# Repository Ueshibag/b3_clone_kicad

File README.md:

# B3 clone KiCad projects, symbols and footprints libraries

## drawbars

A set of 4 interconnected PCBs controlling 38 potentiometers. The left most PCB houses
an Arduino Nano Every which analog to digital converters are used to collect drawbars
positions and send the corresponding MIDI messages to the B3 emulator software (setBfree) running on a Raspberry Pi.

## keyboards

Scans both Fatar keyboards and sends MIDI messages to setBfree

## percussions_expr_pedal

Scans the percussion control switches and performs analog to digital conversion for the
expression pedal. Signals are routed towards the vibrato_chorus_leslie PCB.

## rpi_extension

This is merely a connection PCB for other boards to connect to the Raspberry PI.

## vibrato_chorus_leslie

Scans the vibrato and chorus switches as well as the Leslie 3-position switch (stop/slow/fast).
Gathers signals from the percussions_expr_pedal PCB. Houses an Arduino Nano Every which sends
MIDI messages to setBfree.

## vibrato_chorus_rotary_switch

A small PCB on which the 6-position rotary switch is soldered. This PCB is connected to the
vibrato_chorus_leslie board.

## volume_reverb_overdrive

This board houses three rotary encoders to control IQaudio PiDAC+ volume, setBfree reverb and overdrive. The overdrive rotary switch embeds a push button to safely power down the Raspberry PI.

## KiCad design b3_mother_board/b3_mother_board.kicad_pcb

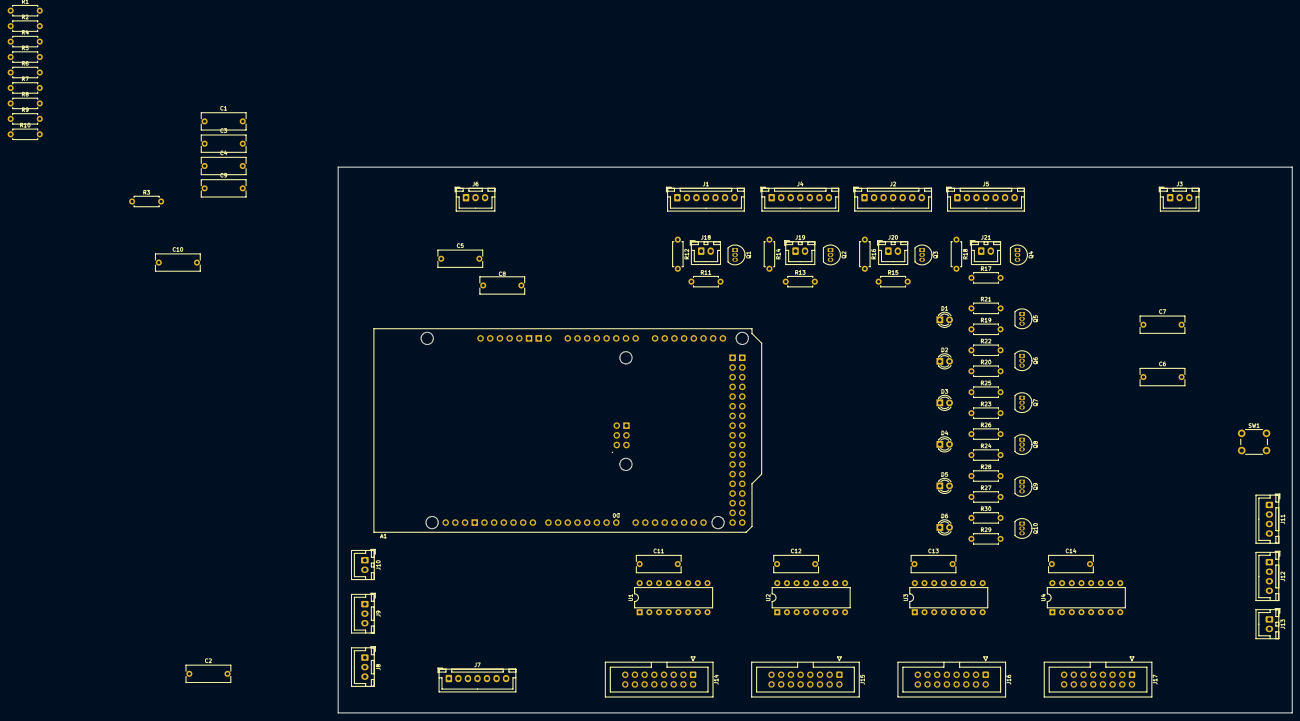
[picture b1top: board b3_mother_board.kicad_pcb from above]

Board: 2 copper layers, 250.0 x 143.0 mm, 87 parts (1 on the bottom side), 127 nets, no tracks yet.

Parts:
A1: Arduino_Mega2560_R3_Shield
C1, C2, C3, C4, C5, C6, C7, C8, C9, C10, C11, C12, C13, C14: 100n; C_Rect_L11.5mm_W4.3mm_P10.00mm_MKT
D1: Keyboards; LED_D3.0mm
D2: Vib/Chr; LED_D3.0mm
D3: Drawbars; LED_D3.0mm
D4: Percussions; LED_D3.0mm
D5: Leslie; LED_D3.0mm
D6: Expression Ped.; LED_D3.0mm
J1: Drawbars_1; JST_XH_B7B-XH-A_1x07_P2.50mm_Vertical
J2: Drawbars_3; JST_XH_B7B-XH-A_1x07_P2.50mm_Vertical
J3: Expression Pedal; JST_XH_B3B-XH-A_1x03_P2.50mm_Vertical
J4: Drawbars_2; JST_XH_B7B-XH-A_1x07_P2.50mm_Vertical
J5: Drawbars_4; JST_XH_B7B-XH-A_1x07_P2.50mm_Vertical
J6: Leslie; JST_XH_B3B-XH-A_1x03_P2.50mm_Vertical
J7: V/C Rotary Knob; JST_XH_B7B-XH-A_1x07_P2.50mm_Vertical
J8: Ovrdrv/Vib LEDs; JST_XH_B3B-XH-A_1x03_P2.50mm_Vertical
J9: Ovrdrv/Vib Switches; JST_XH_B3B-XH-A_1x03_P2.50mm_Vertical
J10: Ovrdrv/Vib PWR; JST_XH_B2B-XH-A_1x02_P2.50mm_Vertical
J11: Percussion LEDs; JST_XH_B4B-XH-A_1x04_P2.50mm_Vertical
J12: Percussion Switches; JST_XH_B4B-XH-A_1x04_P2.50mm_Vertical
J13: Percussion PWR; JST_XH_B2B-XH-A_1x02_P2.50mm_Vertical
J14: Upper Keyboard Left; IDC-Header_2x08_P2.54mm_Vertical
J15: Upper Keyboard Right; IDC-Header_2x08_P2.54mm_Vertical
J16: Lower Keyboard Left; IDC-Header_2x08_P2.54mm_Vertical
J17: Lower Keyboard Right; IDC-Header_2x08_P2.54mm_Vertical
J18: Upper A LED; JST_XH_B2B-XH-A_1x02_P2.50mm_Vertical
J19: Upper B LED; JST_XH_B2B-XH-A_1x02_P2.50mm_Vertical
J20: Lower A LED; JST_XH_B2B-XH-A_1x02_P2.50mm_Vertical
J21: Lower B LED; JST_XH_B2B-XH-A_1x02_P2.50mm_Vertical
Q1, Q2, Q3, Q4, Q5, Q6, Q7, Q8, Q9, Q10: BC547; TO-92_Inline
R1, R2: 68K; R_Axial_DIN0207_L6.3mm_D2.5mm_P7.62mm_Horizontal
R3, R4, R5, R6: 2.2K; R_Axial_DIN0207_L6.3mm_D2.5mm_P7.62mm_Horizontal
R7, R8, R9, R10: 100; R_Axial_DIN0207_L6.3mm_D2.5mm_P7.62mm_Horizontal
R11, R13, R15, R17, R19, R20, R23, R24, R27, R29: 2.8K; R_Axial_DIN0207_L6.3mm_D2.5mm_P7.62mm_Horizontal
R12, R14, R16, R18, R21, R22, R25, R26, R28, R30: 220; R_Axial_DIN0207_L6.3mm_D2.5mm_P7.62mm_Horizontal
SW1: Reset; SW_PUSH_6mm_H4.3mm
U1, U2, U3, U4: 4051; DIP-16_W7.62mm

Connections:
+5V: A1.5V1 (5V), A1.5V2 (SPI_5V), A1.5V3 (5V), A1.5V4 (5V), A1.AREF, C11.1, C12.1, C13.1, C14.1, J1.1, J2.1, J3.1, J4.1, J5.1, J6.1, J10.1, J13.1, R1.1, R12.1, R14.1, R16.1, R18.1, R21.1, R22.1, R25.1, R26.1, R28.1, R30.1, U1.16 (VDD), U2.16 (VDD), U3.16 (VDD), U4.16 (VDD)
/C1: A1.D42, J7.2
/C2: A1.D44, J7.4
/C3: A1.D46, J7.6
/DB_A1_ANLG: A1.A0, C1.1, J1.2
/DB_A2_ANLG: A1.A2, C5.1, J4.2
/DB_A3_ANLG: A1.A4, C2.1, J2.2
/DB_A4_ANLG: A1.A6, C6.1, J5.2
/DB_B1_ANLG: A1.A1, C3.1, J1.3
/DB_B2_ANLG: A1.A3, C7.1, J4.3
/DB_B3_ANLG: A1.A5, C4.1, J2.3
/DB_B4_ANLG: A1.A7, C8.1, J5.3
/DB_MUX_A: A1.D47, J1.4, J2.4, J4.4, J5.4
/DB_MUX_B: A1.D48, J1.5, J2.5, J4.5, J5.5
/DB_MUX_C: A1.D49, J1.6, J2.6, J4.6, J5.6
/DWB_LED: A1.D1 (D1/TX0), R23.1
/EXPR_PEDAL_ANLG: A1.A8, C9.1, J3.2
/EXP_LED: A1.D16 (D16/TX2), R29.1
/KBD_LED: A1.D0 (D0/RX0), R19.1
/LESLIE_ANLG: A1.A9, C10.1, J6.2, R1.2, R2.1
/LO_A_LED: A1.D52 (D52_SCK), R15.1
/LO_B_LED: A1.D53 (D53_CS), R17.1
/LSL_LED: A1.D17 (D17/RX2), R27.1
/OVERDRIVE_LED: A1.D30, J8.1
/OVERDRIVE_SWITCH: A1.D27, J9.1
/PERC_DELAY_LED: A1.D39, J11.3
/PERC_DELAY_SWITCH: A1.D35, J12.3
/PERC_HARMONIC_LED: A1.D40, J11.4
/PERC_HARMONIC_SWITCH: A1.D36, J12.4
/PERC_ON_OFF_LED: A1.D37, J11.1
/PERC_ON_OFF_SWITCH: A1.D33, J12.1
/PERC_VOLUME_LED: A1.D38, J11.2
/PERC_VOLUME_SWITCH: A1.D34, J12.2
/PRC_LED: A1.D18 (D18/TX1), R24.1
/T0: A1.D11, J14.2, J15.2, J16.2, J17.2
/T1: A1.D12, J14.4, J15.4, J16.4, J17.4
/T2: A1.D13, J14.6, J15.6, J16.6, J17.6
/T3: A1.D22, J14.8, J15.8, J16.8, J17.8
/T4: A1.D23, J14.10, J15.10, J16.10, J17.10
/T5: A1.D24, J14.12, J15.12, J16.12, J17.12
/T6: A1.D25, J14.14, J15.14, J16.14, J17.14
/T7: A1.D26, J14.16, J15.16, J16.16, J17.16
/UP_A_LED: A1.D50 (D50_MISO), R11.1
/UP_B_LED: A1.D51 (D51_MOSI), R13.1
/V1: A1.D41, J7.1
/V2: A1.D43, J7.3
/V3: A1.D45, J7.5
/VIBRATO_LOWER_LED: A1.D32, J8.3
/VIBRATO_LOWER_SWITCH: A1.D29, J9.3
/VIBRATO_UPPER_LED: A1.D31, J8.2
/VIBRATO_UPPER_SWITCH: A1.D28, J9.2
/VIB_LED: A1.D19 (D19/RX1), R20.1
/keyboards_control_sub/BRA: A1.D7, R7.1
/keyboards_control_sub/BRA0: J14.3, U1.13 (X0)
/keyboards_control_sub/BRA1: J14.7, U1.14 (X1)
/keyboards_control_sub/BRA2: J14.11, U1.15 (X2)
/keyboards_control_sub/BRA3: J14.15, U1.12 (X3)
/keyboards_control_sub/BRA4: J15.3, U1.1 (X4)
/keyboards_control_sub/BRA5: J15.7, U1.5 (X5)
/keyboards_control_sub/BRA6: J15.11, U1.2 (X6)
/keyboards_control_sub/BRA7: J15.15, U1.4 (X7)
/keyboards_control_sub/BRB: A1.D8, R8.1
/keyboards_control_sub/BRB0: J16.3, U3.13 (X0)
/keyboards_control_sub/BRB1: J16.7, U3.14 (X1)
/keyboards_control_sub/BRB2: J16.11, U3.15 (X2)
/keyboards_control_sub/BRB3: J16.15, U3.12 (X3)
/keyboards_control_sub/BRB4: J17.3, U3.1 (X4)
/keyboards_control_sub/BRB5: J17.7, U3.5 (X5)
/keyboards_control_sub/BRB6: J17.11, U3.2 (X6)
/keyboards_control_sub/BRB7: J17.15, U3.4 (X7)
/keyboards_control_sub/KB_MUX_A: A1.D4, U1.11 (A), U2.11 (A), U3.11 (A), U4.11 (A)
/keyboards_control_sub/KB_MUX_B: A1.D5, U1.10 (B), U2.10 (B), U3.10 (B), U4.10 (B)
/keyboards_control_sub/KB_MUX_C: A1.D6, U1.9 (C), U2.9 (C), U3.9 (C), U4.9 (C)
/keyboards_control_sub/MKA: A1.D9, R9.1
/keyboards_control_sub/MKA0: J14.1, U2.13 (X0)
/keyboards_control_sub/MKA1: J14.5, U2.14 (X1)
/keyboards_control_sub/MKA2: J14.9, U2.15 (X2)
/keyboards_control_sub/MKA3: J14.13, U2.12 (X3)
/keyboards_control_sub/MKA4: J15.1, U2.1 (X4)
/keyboards_control_sub/MKA5: J15.5, U2.5 (X5)
/keyboards_control_sub/MKA6: J15.9, U2.2 (X6)
/keyboards_control_sub/MKA7: J15.13, U2.4 (X7)
/keyboards_control_sub/MKB: A1.D10, R10.1
/keyboards_control_sub/MKB0: J16.1, U4.13 (X0)
/keyboards_control_sub/MKB1: J16.5, U4.14 (X1)
/keyboards_control_sub/MKB2: J16.9, U4.15 (X2)
/keyboards_control_sub/MKB3: J16.13, U4.12 (X3)
/keyboards_control_sub/MKB4: J17.1, U4.1 (X4)
/keyboards_control_sub/MKB5: J17.5, U4.5 (X5)
/keyboards_control_sub/MKB6: J17.9, U4.2 (X6)
/keyboards_control_sub/MKB7: J17.13, U4.4 (X7)
GND: A1.GND1 (GND), A1.GND2 (GND), A1.GND3 (GND), A1.GND4 (SPI_GND), A1.GND5 (GND), A1.GND6 (GND), C1.2, C2.2, C3.2, C4.2, C5.2, C6.2, C7.2, C8.2, C9.2, C10.2, C11.2, C12.2, C13.2, C14.2, J1.7, J2.7, J3.3, J4.7, J5.7, J6.3, J7.7, J10.2, J13.2, Q1.3 (E), Q2.3 (E), Q3.3 (E), Q4.3 (E), Q5.3 (E), Q6.3 (E), Q7.3 (E), Q8.3 (E), Q9.3 (E), Q10.3 (E), R2.2, R3.2, R4.2, R5.2, R6.2, SW1.1, U1.6 (Inh), U1.7 (VEE), U1.8 (VSS), U2.6 (Inh), U2.7 (VEE), U2.8 (VSS), U3.6 (Inh), U3.7 (VEE), U3.8 (VSS), U4.6 (Inh), U4.7 (VEE), U4.8 (VSS)
unnamed: A1.RST1 (RESET), SW1.2
unnamed: D1.2 (A), R21.2
unnamed: D1.1 (K), Q5.1 (C)
unnamed: D2.2 (A), R22.2
unnamed: D2.1 (K), Q6.1 (C)
unnamed: D3.2 (A), R25.2
unnamed: D3.1 (K), Q7.1 (C)
unnamed: D4.2 (A), R26.2
unnamed: D4.1 (K), Q8.1 (C)
unnamed: D5.2 (A), R28.2
unnamed: D5.1 (K), Q9.1 (C)
unnamed: D6.2 (A), R30.2
unnamed: D6.1 (K), Q10.1 (C)
unnamed: J18.1, R12.2
unnamed: J18.2, Q1.1 (C)
unnamed: J19.1, R14.2
unnamed: J19.2, Q2.1 (C)
unnamed: J20.1, R16.2
unnamed: J20.2, Q3.1 (C)
unnamed: J21.1, R18.2
unnamed: J21.2, Q4.1 (C)
unnamed: Q1.2 (B), R11.2
unnamed: Q2.2 (B), R13.2
unnamed: Q3.2 (B), R15.2
unnamed: Q4.2 (B), R17.2
unnamed: Q5.2 (B), R19.2
unnamed: Q6.2 (B), R20.2
unnamed: Q7.2 (B), R23.2
unnamed: Q8.2 (B), R24.2
unnamed: Q9.2 (B), R27.2
unnamed: Q10.2 (B), R29.2
unnamed: R3.1, R7.2, U1.3 (X)
unnamed: R4.1, R9.2, U2.3 (X)
unnamed: R5.1, R8.2, U3.3 (X)
unnamed: R6.1, R10.2, U4.3 (X)

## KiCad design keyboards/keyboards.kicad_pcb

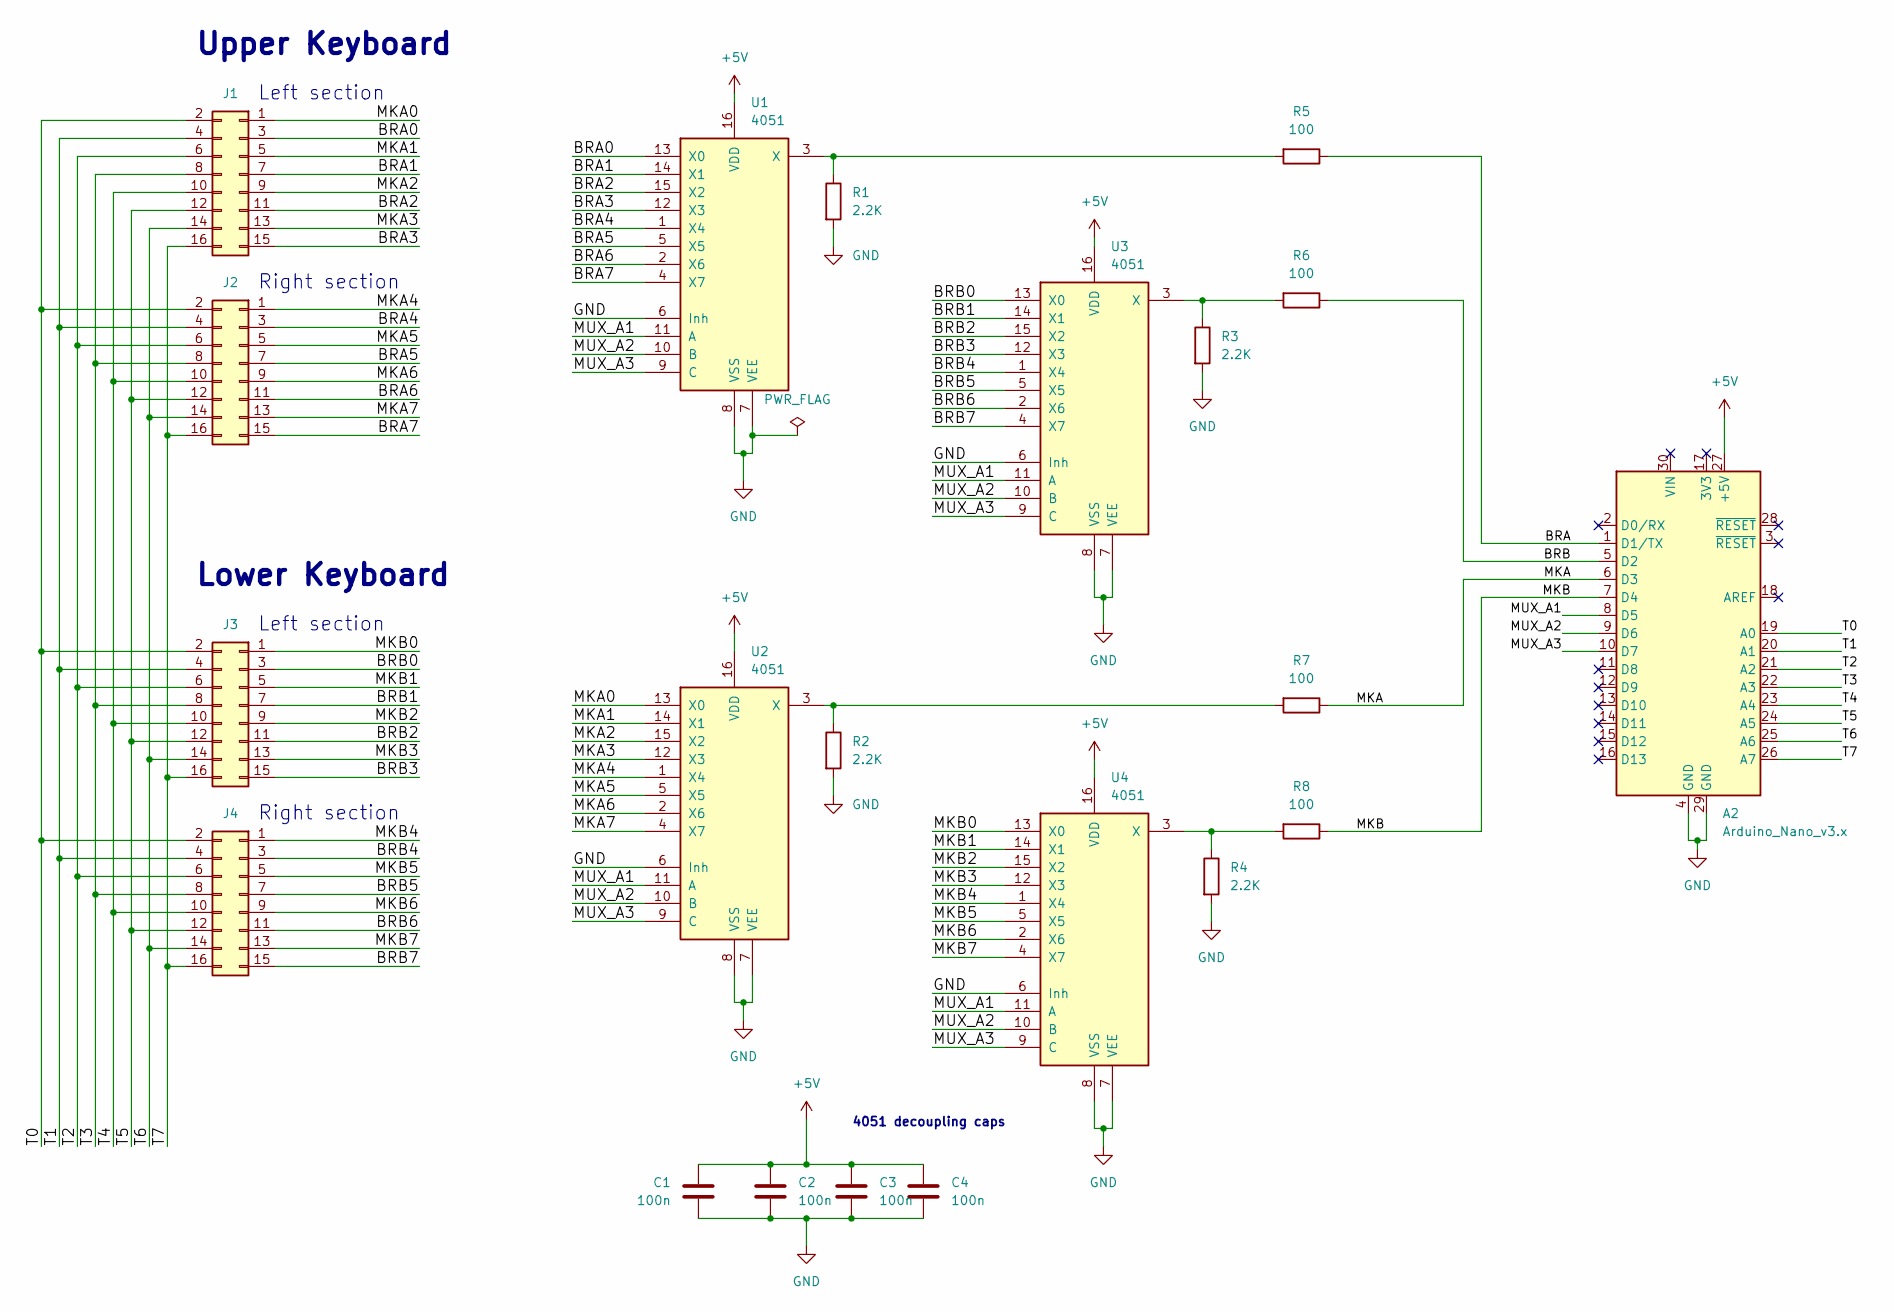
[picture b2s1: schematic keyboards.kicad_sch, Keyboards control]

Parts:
A2: Arduino_Nano_v3.x; Arduino_Nano
C1, C2, C3, C4: 100n; C_1206_3216Metric_Pad1.33x1.80mm_HandSolder
J1, J2, J3, J4: Conn_02x08_Odd_Even; IDC-Header_2x08_P2.54mm_Vertical
R1, R2, R3, R4: 2.2K; R_1206_3216Metric_Pad1.30x1.75mm_HandSolder
R5, R6, R7, R8: 100; R_1206_3216Metric_Pad1.30x1.75mm_HandSolder
U1, U2, U3, U4: 4051; DIP-16_W7.62mm

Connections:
+5V: A2.27 (+5V), C1.1, C2.1, C3.1, C4.1, U1.16 (VDD), U2.16 (VDD), U3.16 (VDD), U4.16 (VDD)
/BRA: A2.1 (D1/TX), R5.1
/BRA0: J1.3, U1.13 (X0)
/BRA1: J1.7, U1.14 (X1)
/BRA2: J1.11, U1.15 (X2)
/BRA3: J1.15, U1.12 (X3)
/BRA4: J2.3, U1.1 (X4)
/BRA5: J2.7, U1.5 (X5)
/BRA6: J2.11, U1.2 (X6)
/BRA7: J2.15, U1.4 (X7)
/BRB: A2.5 (D2), R6.1
/BRB0: J3.3, U3.13 (X0)
/BRB1: J3.7, U3.14 (X1)
/BRB2: J3.11, U3.15 (X2)
/BRB3: J3.15, U3.12 (X3)
/BRB4: J4.3, U3.1 (X4)
/BRB5: J4.7, U3.5 (X5)
/BRB6: J4.11, U3.2 (X6)
/BRB7: J4.15, U3.4 (X7)
/MKA: A2.6 (D3), R7.1
/MKA0: J1.1, U2.13 (X0)
/MKA1: J1.5, U2.14 (X1)
/MKA2: J1.9, U2.15 (X2)
/MKA3: J1.13, U2.12 (X3)
/MKA4: J2.1, U2.1 (X4)
/MKA5: J2.5, U2.5 (X5)
/MKA6: J2.9, U2.2 (X6)
/MKA7: J2.13, U2.4 (X7)
/MKB: A2.7 (D4), R8.1
/MKB0: J3.1, U4.13 (X0)
/MKB1: J3.5, U4.14 (X1)
/MKB2: J3.9, U4.15 (X2)
/MKB3: J3.13, U4.12 (X3)
/MKB4: J4.1, U4.1 (X4)
/MKB5: J4.5, U4.5 (X5)
/MKB6: J4.9, U4.2 (X6)
/MKB7: J4.13, U4.4 (X7)
/MUX_A1: A2.8 (D5), U1.11 (A), U2.11 (A), U3.11 (A), U4.11 (A)
/MUX_A2: A2.9 (D6), U1.10 (B), U2.10 (B), U3.10 (B), U4.10 (B)
/MUX_A3: A2.10 (D7), U1.9 (C), U2.9 (C), U3.9 (C), U4.9 (C)
/T0: A2.19 (A0), J1.2, J2.2, J3.2, J4.2
/T1: A2.20 (A1), J1.4, J2.4, J3.4, J4.4
/T2: A2.21 (A2), J1.6, J2.6, J3.6, J4.6
/T3: A2.22 (A3), J1.8, J2.8, J3.8, J4.8
/T4: A2.23 (A4), J1.10, J2.10, J3.10, J4.10
/T5: A2.24 (A5), J1.12, J2.12, J3.12, J4.12
/T6: A2.25 (A6), J1.14, J2.14, J3.14, J4.14
/T7: A2.26 (A7), J1.16, J2.16, J3.16, J4.16
GND: A2.4 (GND), A2.29 (GND), C1.2, C2.2, C3.2, C4.2, R1.2, R2.2, R3.2, R4.2, U1.6 (Inh), U1.7 (VEE), U1.8 (VSS), U2.6 (Inh), U2.7 (VEE), U2.8 (VSS), U3.6 (Inh), U3.7 (VEE), U3.8 (VSS), U4.6 (Inh), U4.7 (VEE), U4.8 (VSS)
unnamed: R1.1, R5.2, U1.3 (X)
unnamed: R2.1, R7.2, U2.3 (X)
unnamed: R3.1, R6.2, U3.3 (X)
unnamed: R4.1, R8.2, U4.3 (X)

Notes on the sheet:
Left section
Lower Keyboard
4051 decoupling caps
Upper Keyboard
Right section

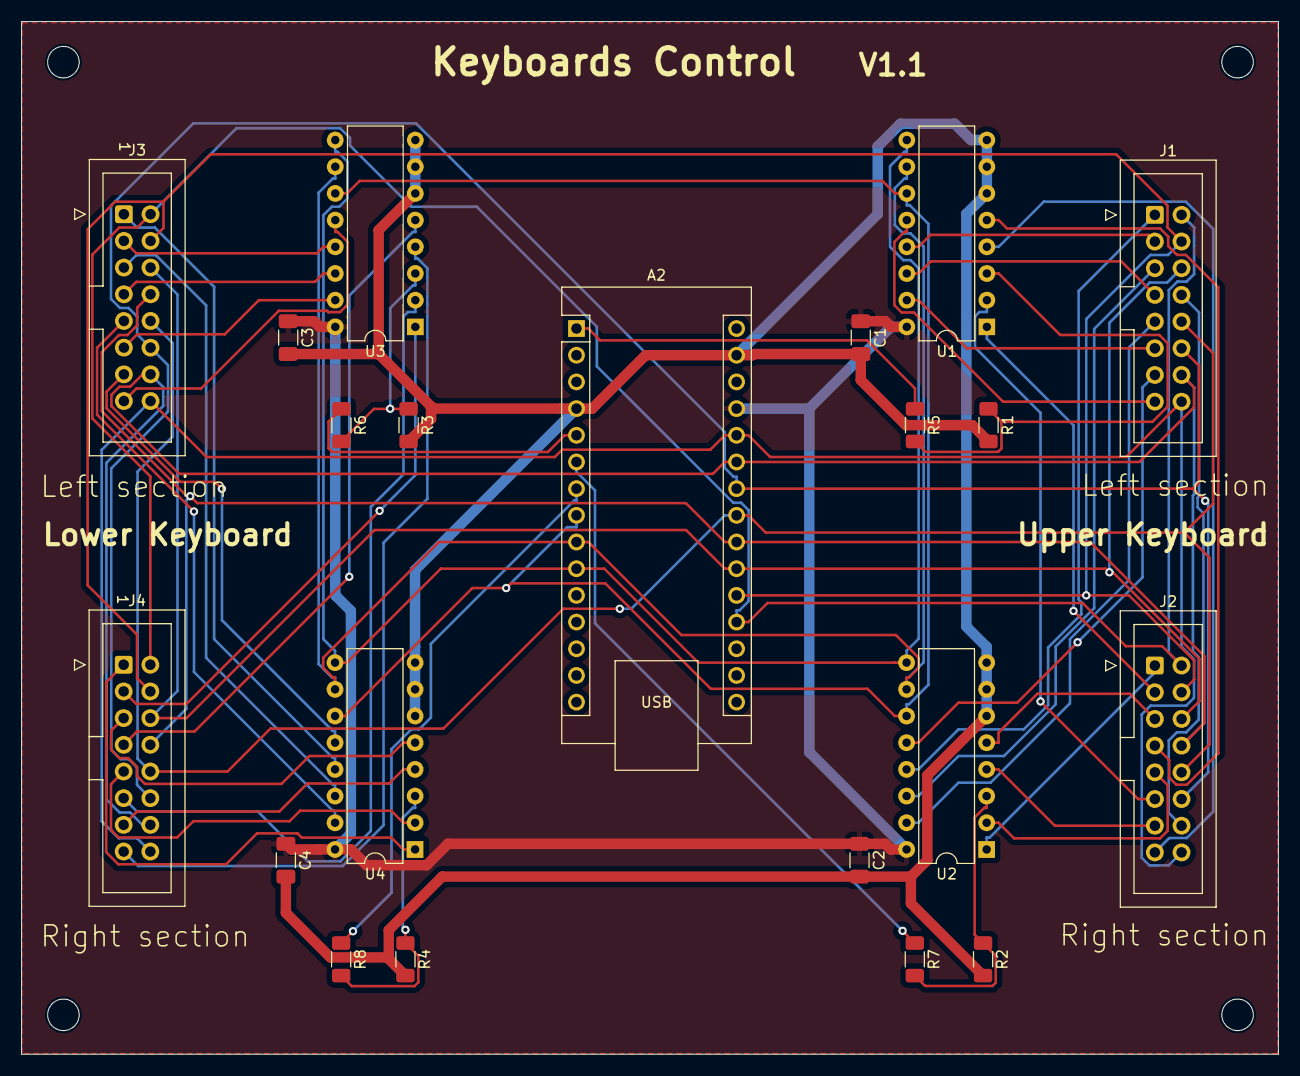
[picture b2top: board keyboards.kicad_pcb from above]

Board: 2 copper layers, 119.6 x 98.3 mm, 25 parts (0 on the bottom side), 53 nets.

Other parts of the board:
REF1, REF2, REF3, REF4: MountingHole_3mm

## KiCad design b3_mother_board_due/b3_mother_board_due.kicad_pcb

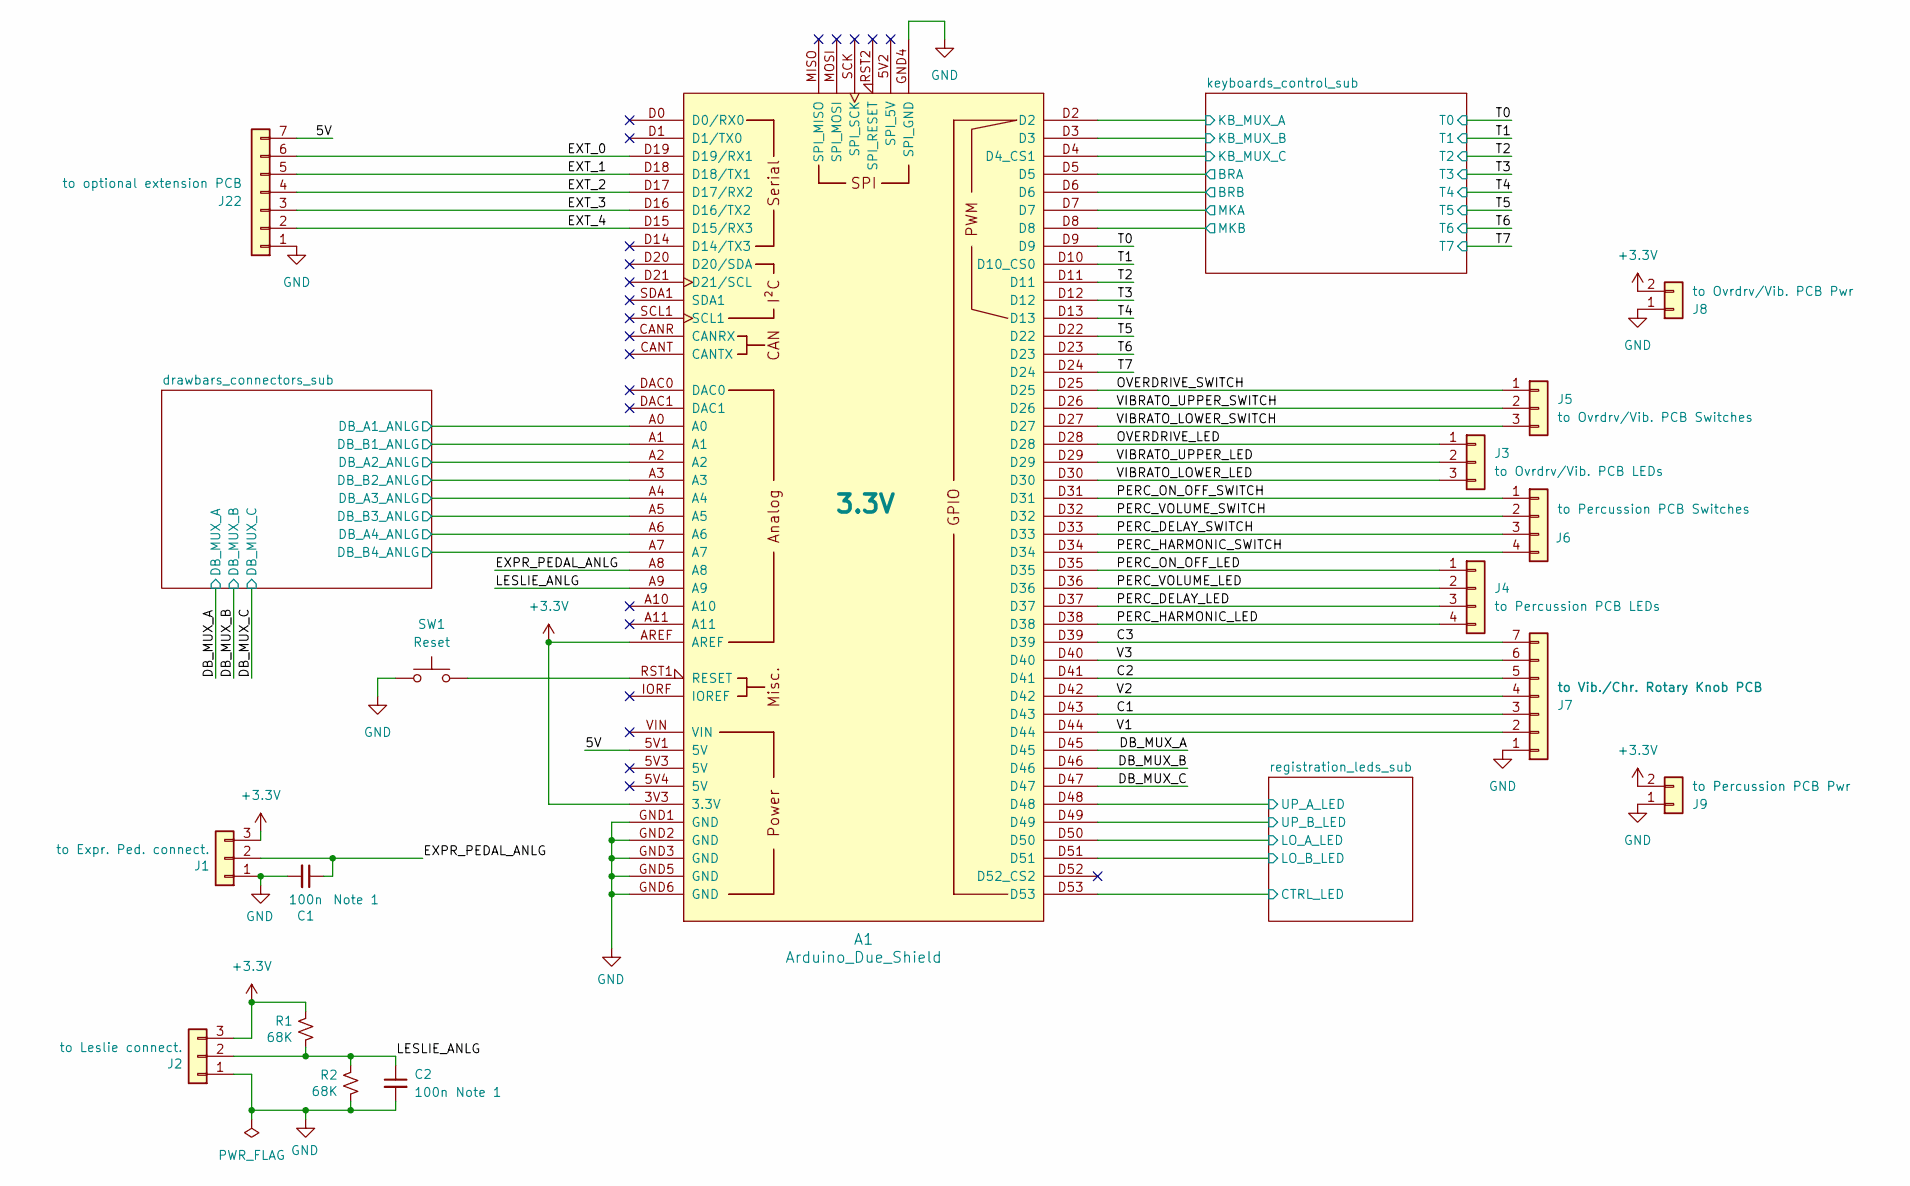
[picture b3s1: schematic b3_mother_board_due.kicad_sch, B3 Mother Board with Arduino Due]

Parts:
A1: Arduino_Due_Shield; Voltage 3.3V
C1, C2: 100n; C_Rect_L11.5mm_W4.3mm_P10.00mm_MKT
J1: to Expr. Ped. connect.; JST_XH_B3B-XH-A_1x03_P2.50mm_Vertical
J2: to Leslie connect.; JST_XH_B3B-XH-A_1x03_P2.50mm_Vertical
J3: to Ovrdrv/Vib. PCB LEDs; JST_XH_B3B-XH-A_1x03_P2.50mm_Vertical
J4: to Percussion PCB LEDs; JST_XH_B4B-XH-A_1x04_P2.50mm_Vertical
J5: to Ovrdrv/Vib. PCB Switches; JST_XH_B3B-XH-A_1x03_P2.50mm_Vertical
J6: to Percussion PCB Switches; JST_XH_B4B-XH-A_1x04_P2.50mm_Vertical
J7: to Vib./Chr. Rotary Knob PCB; JST_XH_B7B-XH-A_1x07_P2.50mm_Vertical
J8: to Ovrdrv/Vib. PCB Pwr; JST_XH_B2B-XH-A_1x02_P2.50mm_Vertical
J9: to Percussion PCB Pwr; JST_XH_B2B-XH-A_1x02_P2.50mm_Vertical
J22: to optional extension PCB; JST_XH_B7B-XH-A_1x07_P2.50mm_Vertical
R1, R2: 68K; R_Axial_DIN0207_L6.3mm_D2.5mm_P7.62mm_Horizontal
SW1: Reset; SW_PUSH_6mm_H4.3mm

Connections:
+3.3V: A1.3V3 (3.3V), A1.AREF, J1.3, J2.3, J8.2, J9.2, R1.1; also elsewhere on the board
/5V: A1.5V1 (5V), J22.7
/C1: A1.D43, J7.3
/C2: A1.D41, J7.5
/C3: A1.D39, J7.7
/DB_MUX_A: A1.D45; also elsewhere on the board
/DB_MUX_B: A1.D46; also elsewhere on the board
/DB_MUX_C: A1.D47; also elsewhere on the board
/EXPR_PEDAL_ANLG: A1.A8, C1.1, J1.2
/EXT_0: A1.D19 (D19/RX1), J22.6
/EXT_1: A1.D18 (D18/TX1), J22.5
/EXT_2: A1.D17 (D17/RX2), J22.4
/EXT_3: A1.D16 (D16/TX2), J22.3
/EXT_4: A1.D15 (D15/RX3), J22.2
/LESLIE_ANLG: A1.A9, C2.1, J2.2, R1.2, R2.1
/OVERDRIVE_LED: A1.D28, J3.1
/OVERDRIVE_SWITCH: A1.D25, J5.1
/PERC_DELAY_LED: A1.D37, J4.3
/PERC_DELAY_SWITCH: A1.D33, J6.3
/PERC_HARMONIC_LED: A1.D38, J4.4
/PERC_HARMONIC_SWITCH: A1.D34, J6.4
/PERC_ON_OFF_LED: A1.D35, J4.1
/PERC_ON_OFF_SWITCH: A1.D31, J6.1
/PERC_VOLUME_LED: A1.D36, J4.2
/PERC_VOLUME_SWITCH: A1.D32, J6.2
/T0: A1.D9; also elsewhere on the board
/T1: A1.D10 (D10_CS0); also elsewhere on the board
/T2: A1.D11; also elsewhere on the board
/T3: A1.D12; also elsewhere on the board
/T4: A1.D13; also elsewhere on the board
/T5: A1.D22; also elsewhere on the board
/T6: A1.D23; also elsewhere on the board
/T7: A1.D24; also elsewhere on the board
/V1: A1.D44, J7.2
/V2: A1.D42, J7.4
/V3: A1.D40, J7.6
/VIBRATO_LOWER_LED: A1.D30, J3.3
/VIBRATO_LOWER_SWITCH: A1.D27, J5.3
/VIBRATO_UPPER_LED: A1.D29, J3.2
/VIBRATO_UPPER_SWITCH: A1.D26, J5.2
/drawbars_connectors_sub/DB_A1_ANLG: A1.A0; also elsewhere on the board
/drawbars_connectors_sub/DB_A2_ANLG: A1.A2; also elsewhere on the board
/drawbars_connectors_sub/DB_A3_ANLG: A1.A4; also elsewhere on the board
/drawbars_connectors_sub/DB_A4_ANLG: A1.A6; also elsewhere on the board
/drawbars_connectors_sub/DB_B1_ANLG: A1.A1; also elsewhere on the board
/drawbars_connectors_sub/DB_B2_ANLG: A1.A3; also elsewhere on the board
/drawbars_connectors_sub/DB_B3_ANLG: A1.A5; also elsewhere on the board
/drawbars_connectors_sub/DB_B4_ANLG: A1.A7; also elsewhere on the board
/keyboards_control_sub/BRA: A1.D5; also elsewhere on the board
/keyboards_control_sub/BRB: A1.D6; also elsewhere on the board
/keyboards_control_sub/KB_MUX_A: A1.D2; also elsewhere on the board
/keyboards_control_sub/KB_MUX_B: A1.D3; also elsewhere on the board
/keyboards_control_sub/KB_MUX_C: A1.D4 (D4_CS1); also elsewhere on the board
/keyboards_control_sub/MKA: A1.D7; also elsewhere on the board
/keyboards_control_sub/MKB: A1.D8; also elsewhere on the board
/registration_leds_sub/CTRL_LED: A1.D53; also elsewhere on the board
/registration_leds_sub/LO_A_LED: A1.D50; also elsewhere on the board
/registration_leds_sub/LO_B_LED: A1.D51; also elsewhere on the board
/registration_leds_sub/UP_A_LED: A1.D48; also elsewhere on the board
/registration_leds_sub/UP_B_LED: A1.D49; also elsewhere on the board
GND: A1.GND1 (GND), A1.GND2 (GND), A1.GND3 (GND), A1.GND4 (SPI_GND), A1.GND5 (GND), A1.GND6 (GND), C1.2, C2.2, J1.1, J2.1, J7.1, J8.1, J9.1, J22.1, R2.2, SW1.1; also elsewhere on the board
unnamed: A1.RST1 (RESET), SW1.2

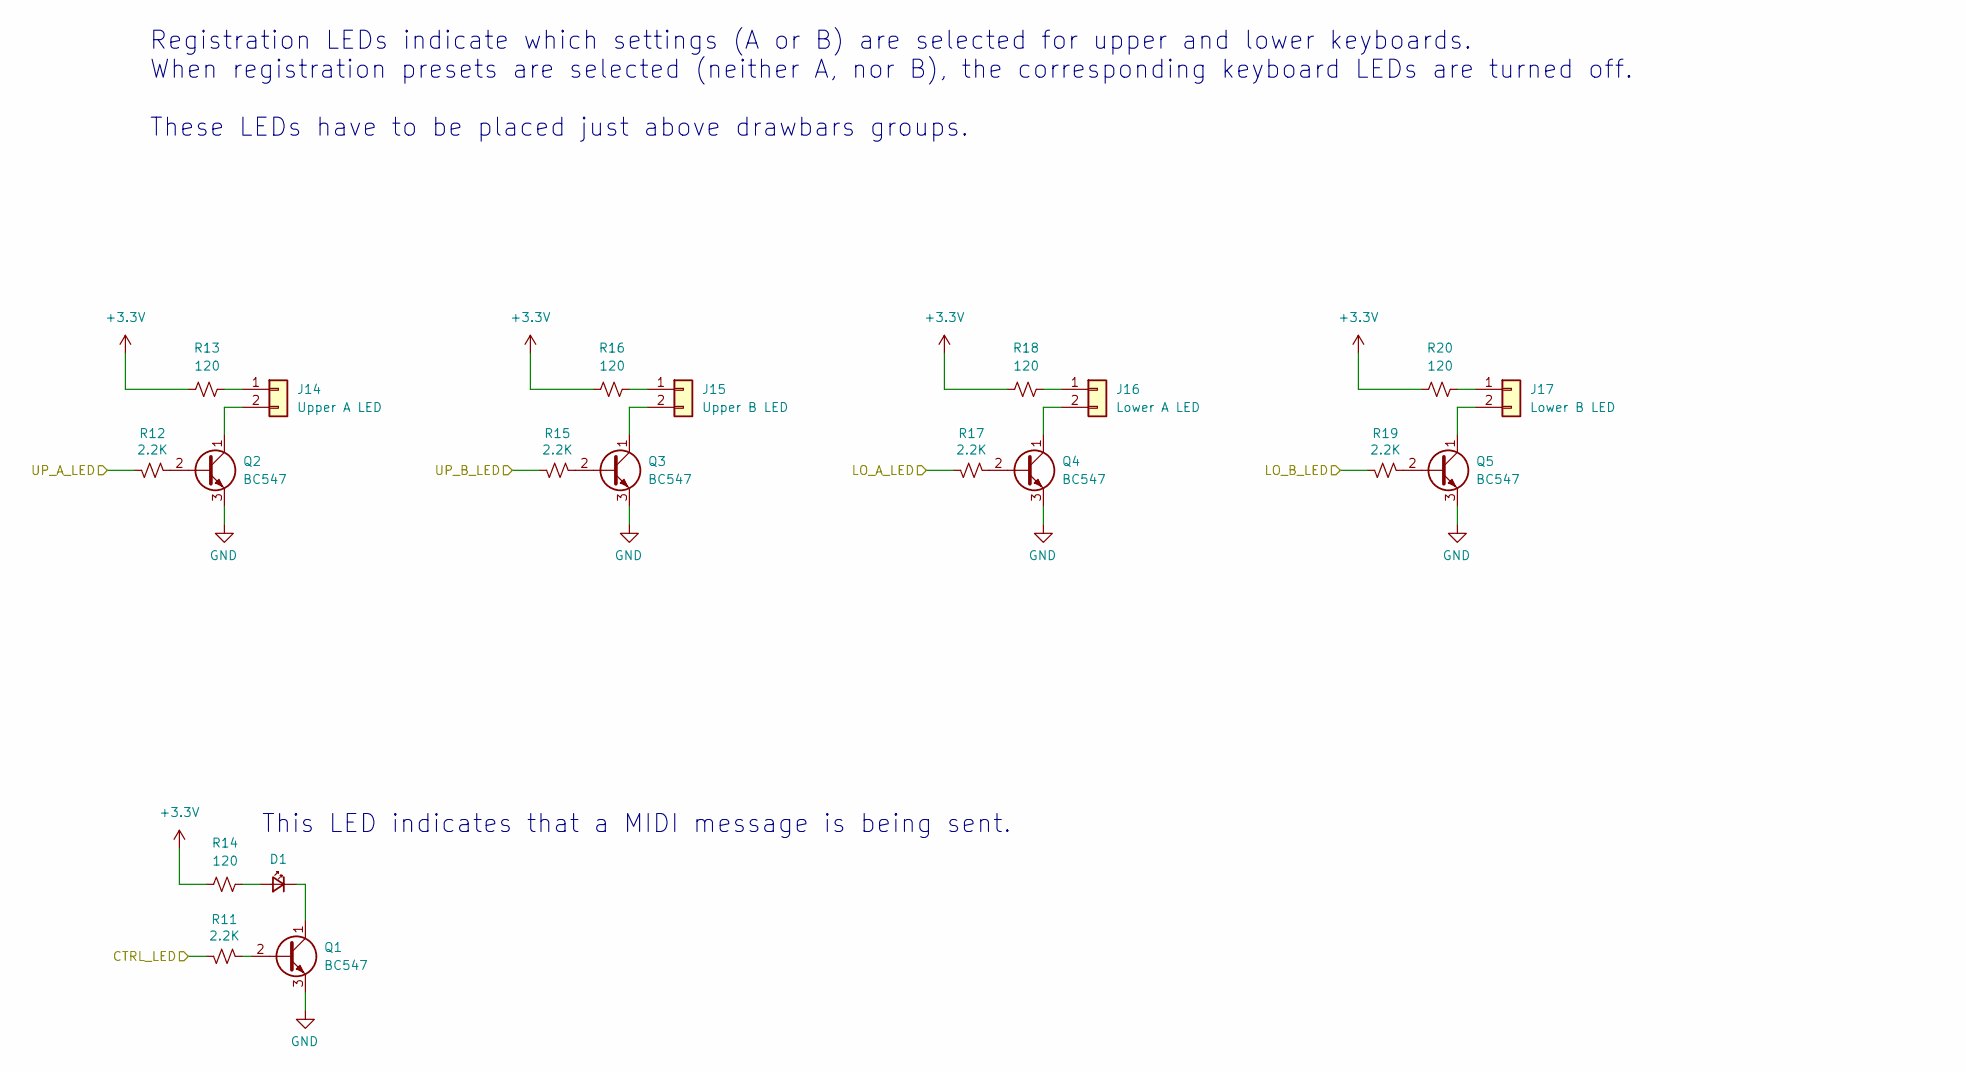
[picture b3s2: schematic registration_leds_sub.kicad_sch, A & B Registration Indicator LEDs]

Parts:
D1: Keyboards; LED_D3.0mm
J14: Upper A LED; JST_XH_B2B-XH-A_1x02_P2.50mm_Vertical
J15: Upper B LED; JST_XH_B2B-XH-A_1x02_P2.50mm_Vertical
J16: Lower A LED; JST_XH_B2B-XH-A_1x02_P2.50mm_Vertical
J17: Lower B LED; JST_XH_B2B-XH-A_1x02_P2.50mm_Vertical
Q1, Q2, Q3, Q4, Q5: BC547; TO-92_Inline
R11, R12, R15, R17, R19: 2.2K; R_Axial_DIN0207_L6.3mm_D2.5mm_P7.62mm_Horizontal
R13, R14, R16, R18, R20: 120; R_Axial_DIN0207_L6.3mm_D2.5mm_P7.62mm_Horizontal

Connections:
+3.3V: R13.1, R14.1, R16.1, R18.1, R20.1; also elsewhere on the board
/registration_leds_sub/CTRL_LED: R11.1; also elsewhere on the board
/registration_leds_sub/LO_A_LED: R17.1; also elsewhere on the board
/registration_leds_sub/LO_B_LED: R19.1; also elsewhere on the board
/registration_leds_sub/UP_A_LED: R12.1; also elsewhere on the board
/registration_leds_sub/UP_B_LED: R15.1; also elsewhere on the board
GND: Q1.3 (E), Q2.3 (E), Q3.3 (E), Q4.3 (E), Q5.3 (E); also elsewhere on the board
unnamed: D1.2 (A), R14.2
unnamed: D1.1 (K), Q1.1 (C)
unnamed: J14.1, R13.2
unnamed: J14.2, Q2.1 (C)
unnamed: J15.1, R16.2
unnamed: J15.2, Q3.1 (C)
unnamed: J16.1, R18.2
unnamed: J16.2, Q4.1 (C)
unnamed: J17.1, R20.2
unnamed: J17.2, Q5.1 (C)
unnamed: Q1.2 (B), R11.2
unnamed: Q2.2 (B), R12.2
unnamed: Q3.2 (B), R15.2
unnamed: Q4.2 (B), R17.2
unnamed: Q5.2 (B), R19.2

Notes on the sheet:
Registration LEDs indicate which settings (A or B) are selected for upper and lower keyboards. When registration presets are selected (neither A, nor B), the corresponding keyboard LEDs are turned off. These LEDs have to be placed just above drawbars groups.
This LED indicates that a MIDI message is being sent.

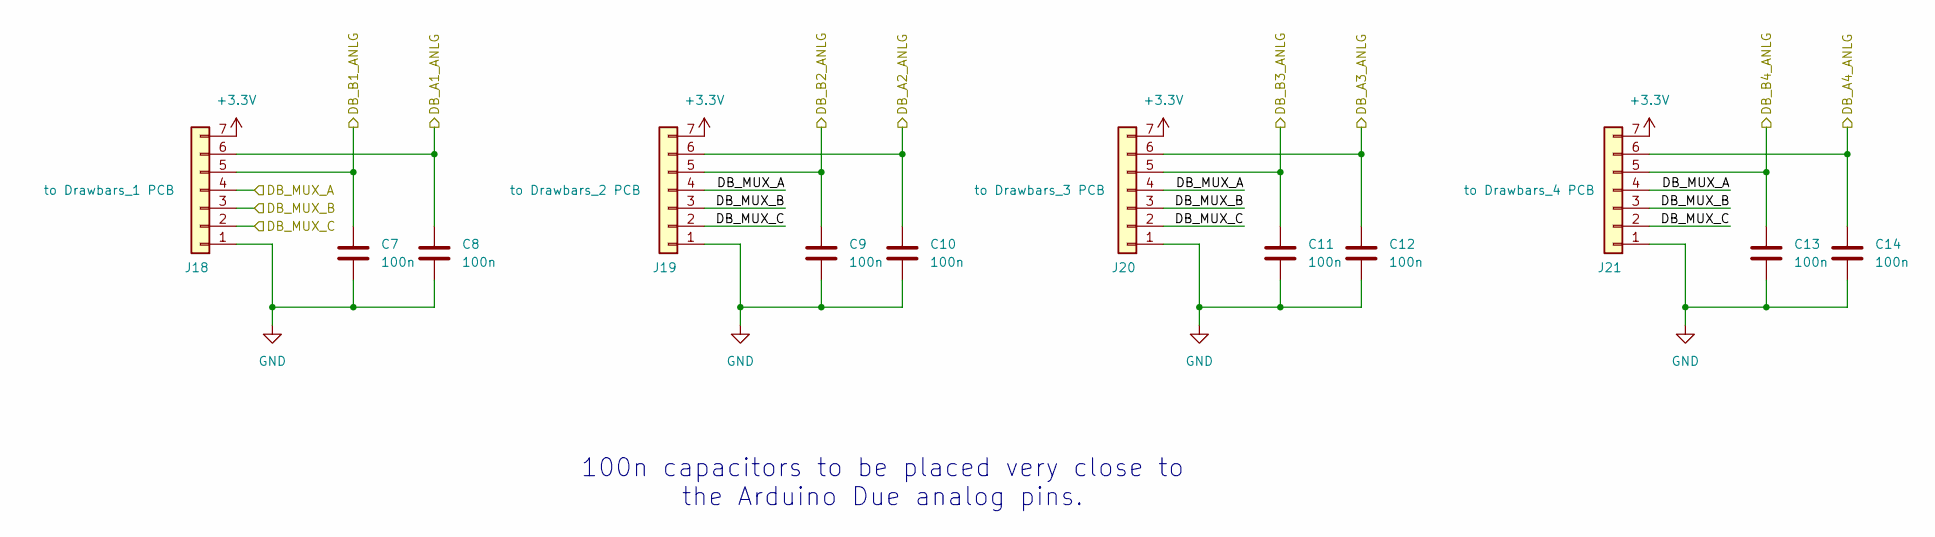
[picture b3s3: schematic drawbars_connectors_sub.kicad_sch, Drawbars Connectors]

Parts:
C7, C8, C9, C10, C11, C12, C13, C14: 100n; C_Rect_L11.5mm_W4.3mm_P10.00mm_MKT
J18: to Drawbars_1 PCB; JST_XH_B7B-XH-A_1x07_P2.50mm_Vertical
J19: to Drawbars_2 PCB; JST_XH_B7B-XH-A_1x07_P2.50mm_Vertical
J20: to Drawbars_3 PCB; JST_XH_B7B-XH-A_1x07_P2.50mm_Vertical
J21: to Drawbars_4 PCB; JST_XH_B7B-XH-A_1x07_P2.50mm_Vertical

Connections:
+3.3V: J18.7, J19.7, J20.7, J21.7; also elsewhere on the board
/DB_MUX_A: J18.4, J19.4, J20.4, J21.4; also elsewhere on the board
/DB_MUX_B: J18.3, J19.3, J20.3, J21.3; also elsewhere on the board
/DB_MUX_C: J18.2, J19.2, J20.2, J21.2; also elsewhere on the board
/drawbars_connectors_sub/DB_A1_ANLG: C8.1, J18.6; also elsewhere on the board
/drawbars_connectors_sub/DB_A2_ANLG: C10.1, J19.6; also elsewhere on the board
/drawbars_connectors_sub/DB_A3_ANLG: C12.1, J20.6; also elsewhere on the board
/drawbars_connectors_sub/DB_A4_ANLG: C14.1, J21.6; also elsewhere on the board
/drawbars_connectors_sub/DB_B1_ANLG: C7.1, J18.5; also elsewhere on the board
/drawbars_connectors_sub/DB_B2_ANLG: C9.1, J19.5; also elsewhere on the board
/drawbars_connectors_sub/DB_B3_ANLG: C11.1, J20.5; also elsewhere on the board
/drawbars_connectors_sub/DB_B4_ANLG: C13.1, J21.5; also elsewhere on the board
GND: C7.2, C8.2, C9.2, C10.2, C11.2, C12.2, C13.2, C14.2, J18.1, J19.1, J20.1, J21.1; also elsewhere on the board

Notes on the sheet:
100n capacitors to be placed very close to the Arduino Due analog pins.

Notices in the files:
parts and their libraries:
Copyright 2021 Accelerated Designs. All rights reserved.
